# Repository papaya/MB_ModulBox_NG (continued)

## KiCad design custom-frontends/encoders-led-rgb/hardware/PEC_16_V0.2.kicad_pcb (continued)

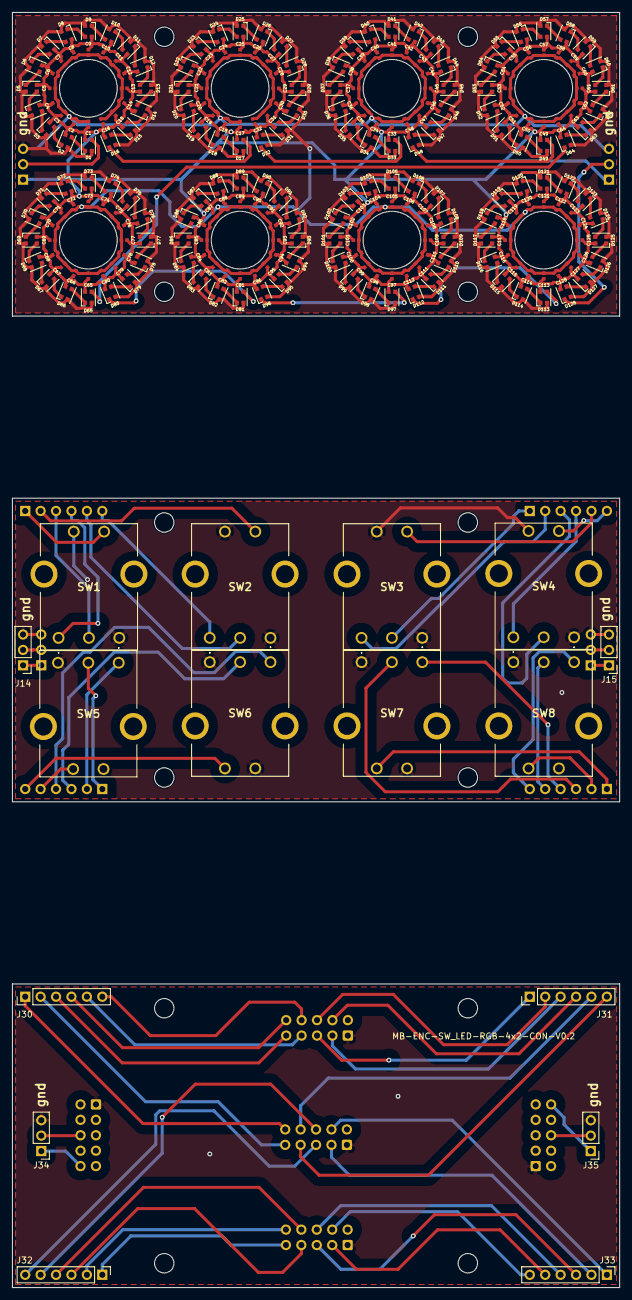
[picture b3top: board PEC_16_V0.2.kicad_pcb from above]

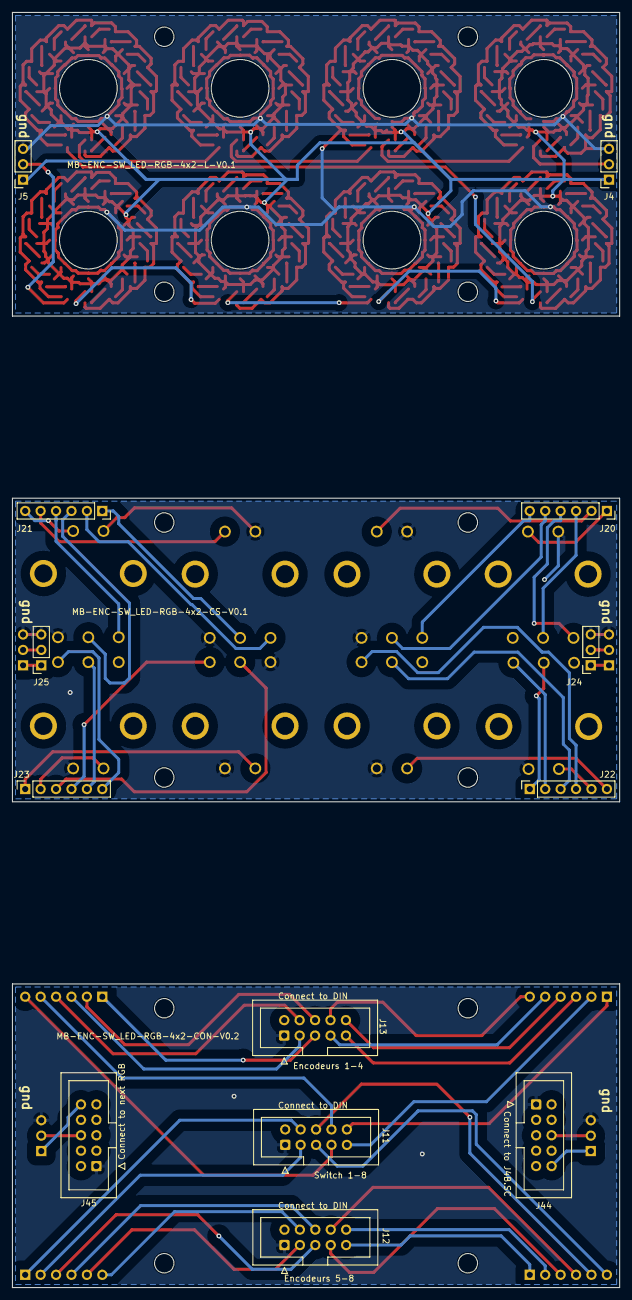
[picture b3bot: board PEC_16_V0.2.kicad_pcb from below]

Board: 2 copper layers, 100.0 x 50.0 mm, 305 parts (13 on the bottom side), 189 nets.

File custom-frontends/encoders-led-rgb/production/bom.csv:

Designator,Footprint,Quantity,Value,LCSC Part #
"C1, C10, C100, C101, C102, C103, C104, C105, C106, C107, C108, C109, C11, C110, C111, C112, C113, C114, C115, C116, C117, C118, C119, C12, C120, C121, C122, C123, C124, C125, C126, C127, C128, C13, C14, C15, C16, C17, C18, C19, C2, C20, C21, C22, C23, C24, C25, C26, C27, C28, C29, C3, C30, C31, C32, C33, C34, C35, C36, C37, C38, C39, C4, C40, C41, C42, C43, C44, C45, C46, C47, C48, C49, C5, C50, C51, C52, C53, C54, C55, C56, C57, C58, C59, C6, C60, C61, C62, C63, C64, C65, C66, C67, C68, C69, C7, C70, C71, C72, C73, C74, C75, C76, C77, C78, C79, C8, C80, C81, C82, C83, C84, C85, C86, C87, C88, C89, C9, C90, C91, C92, C93, C94, C95, C96, C97, C98, C99",CAPC1005X55N,128,100nf,C1525
"D1, D10, D100, D101, D102, D103, D104, D105, D106, D107, D108, D109, D11, D110, D111, D112, D113, D114, D115, D116, D117, D118, D119, D12, D120, D121, D122, D123, D124, D125, D126, D127, D128, D13, D14, D15, D16, D17, D18, D19, D2, D20, D21, D22, D23, D24, D25, D26, D27, D28, D29, D3, D30, D31, D32, D33, D34, D35, D36, D37, D38, D39, D4, D40, D41, D42, D43, D44, D45, D46, D47, D48, D49, D5, D50, D51, D52, D53, D54, D55, D56, D57, D58, D59, D6, D60, D61, D62, D63, D64, D65, D66, D67, D68, D69, D7, D70, D71, D72, D73, D74, D75, D76, D77, D78, D79, D8, D80, D81, D82, D83, D84, D85, D86, D87, D88, D89, D9, D90, D91, D92, D93, D94, D95, D96, D97, D98, D99",LED_WS2812B-2020_PLCC4_2.0x2.0mm,128,WS2812-2020,C2976072
"H1, H13, H14, H15, H16, H17, H18, H19, H2, H20, H3, H4",MountingHole_3.2mm_M3,12,MountingHole,
"H10, H11, H12, H5, H6, H7, H8, H9",Hole_9.5mm,8,MountingHole,
"J11, J12, J13",IDC-Header_2x05_P2.54mm_Vertical_ksr_dIN,3,sin_in,
"J14, J15, J34, J35",PinHeader_1x03_P2.54mm_Vertical,4,Conn_01x06_Pin,
"J20, J21, J22, J23",PinSocket_1x06_P2.54mm_Vertical,4,Conn_01x06_Socket,
"J24, J25, J4, J5",PinSocket_1x03_P2.54mm_Vertical,4,Conn_01x06_Socket,
"J30, J31, J32, J33",PinHeader_1x06_P2.54mm_Vertical,4,Conn_01x06_Pin,
"J44, J45",IDC-Header_2x05_P2.54mm_Vertical,2,IDC-Header_2x05_P2.54mm_Vertical,
"SW1, SW2, SW3, SW4, SW5, SW6, SW7, SW8",PEC164120FS0012,8,PEC16-4XXXF-SXXXX,

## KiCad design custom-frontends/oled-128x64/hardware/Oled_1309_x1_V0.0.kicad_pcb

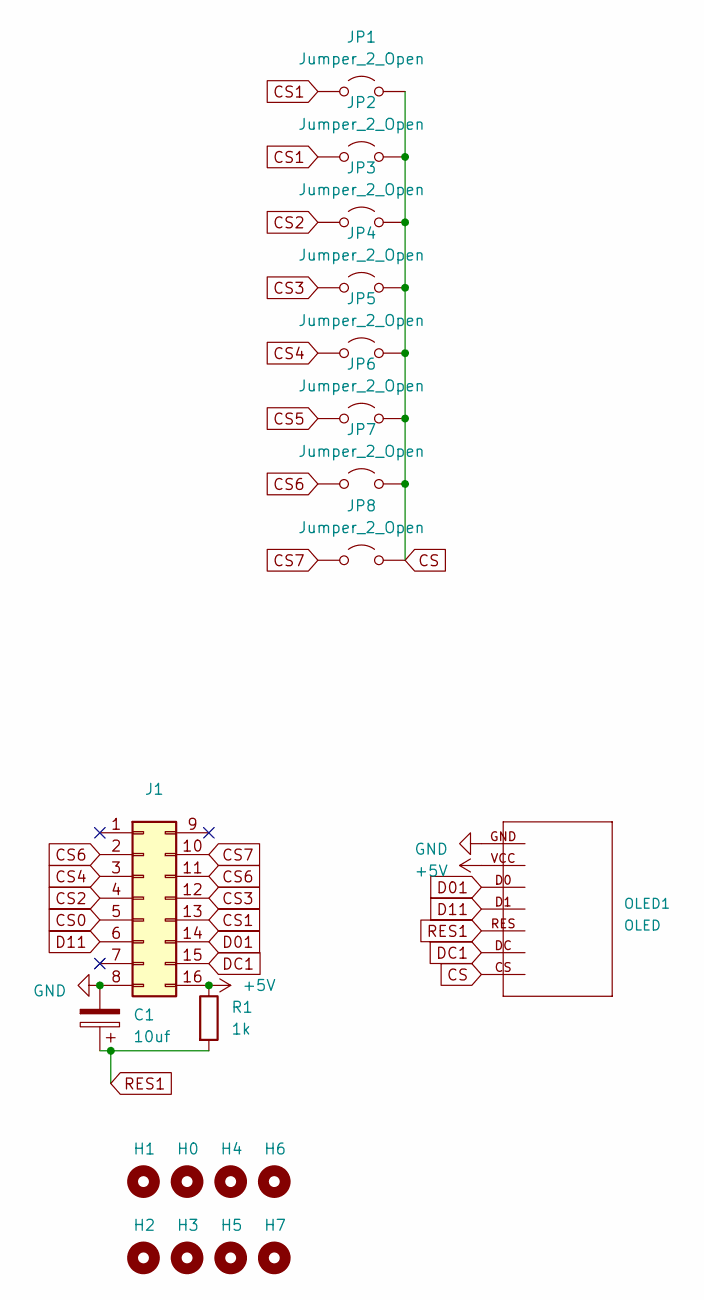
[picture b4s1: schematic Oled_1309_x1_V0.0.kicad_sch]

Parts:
C1: 10uf; CP_Radial_D5.0mm_P2.00mm
H0, H1, H2, H3, H4, H5, H6, H7: MountingHole; MountingHole_2.2mm_M2
J1: IDC-Header_2x08_P2.54mm_Vertical
JP1, JP2, JP3, JP4, JP5, JP6, JP7, JP8: Jumper_2_Open; PinHeader_1x02_P2.54mm_Vertical
OLED1: OLED; SSD_1309
R1: 1k; R_Axial_DIN0204_L3.6mm_D1.6mm_P5.08mm_Horizontal

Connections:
+5V: J1.16, OLED1.VCC, R1.1
CS: JP1.2 (B), JP2.2 (B), JP3.2 (B), JP4.2 (B), JP5.2 (B), JP6.2 (B), JP7.2 (B), JP8.2 (B), OLED1.CS
CS0: J1.5
CS1: J1.13, JP1.1 (A), JP2.1 (A)
CS2: J1.4, JP3.1 (A)
CS3: J1.12, JP4.1 (A)
CS4: J1.3, JP5.1 (A)
CS5: JP6.1 (A)
CS6: J1.2, J1.11, JP7.1 (A)
CS7: J1.10, JP8.1 (A)
D01: J1.14, OLED1.D0
D11: J1.6, OLED1.D1
DC1: J1.15, OLED1.DC
GND: C1.2, J1.8, OLED1.GND
RES1: C1.1, OLED1.RES, R1.2

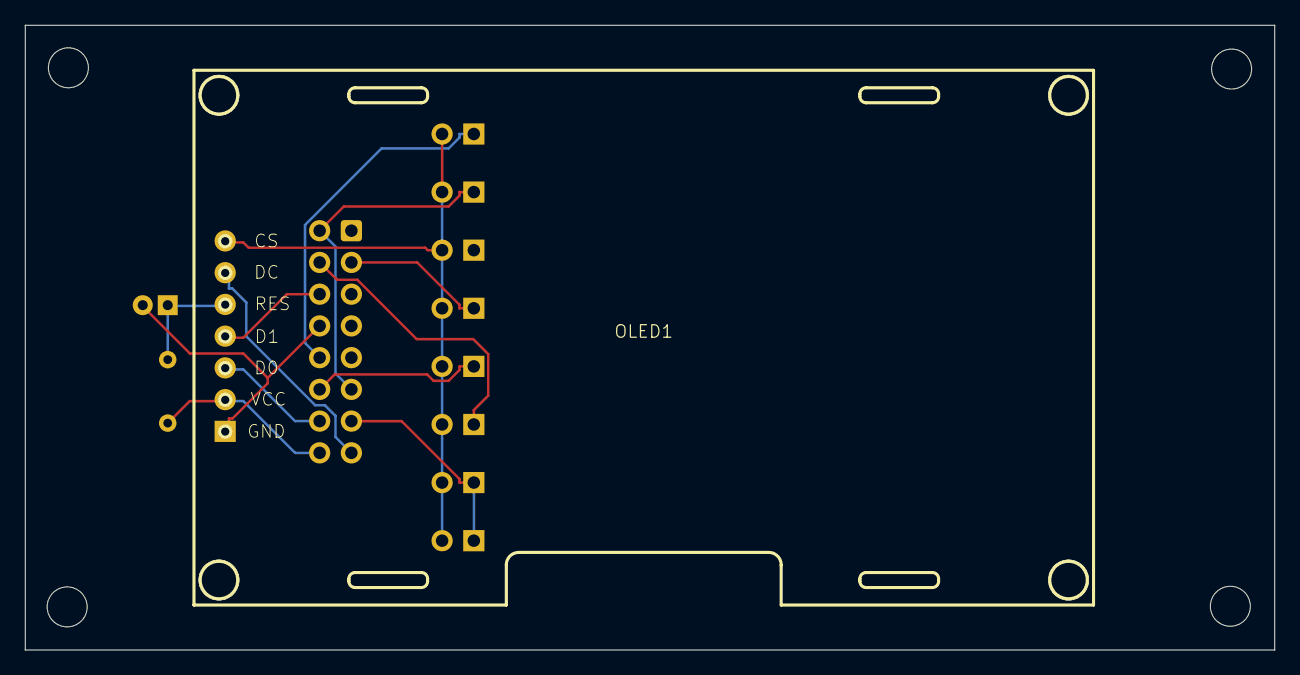
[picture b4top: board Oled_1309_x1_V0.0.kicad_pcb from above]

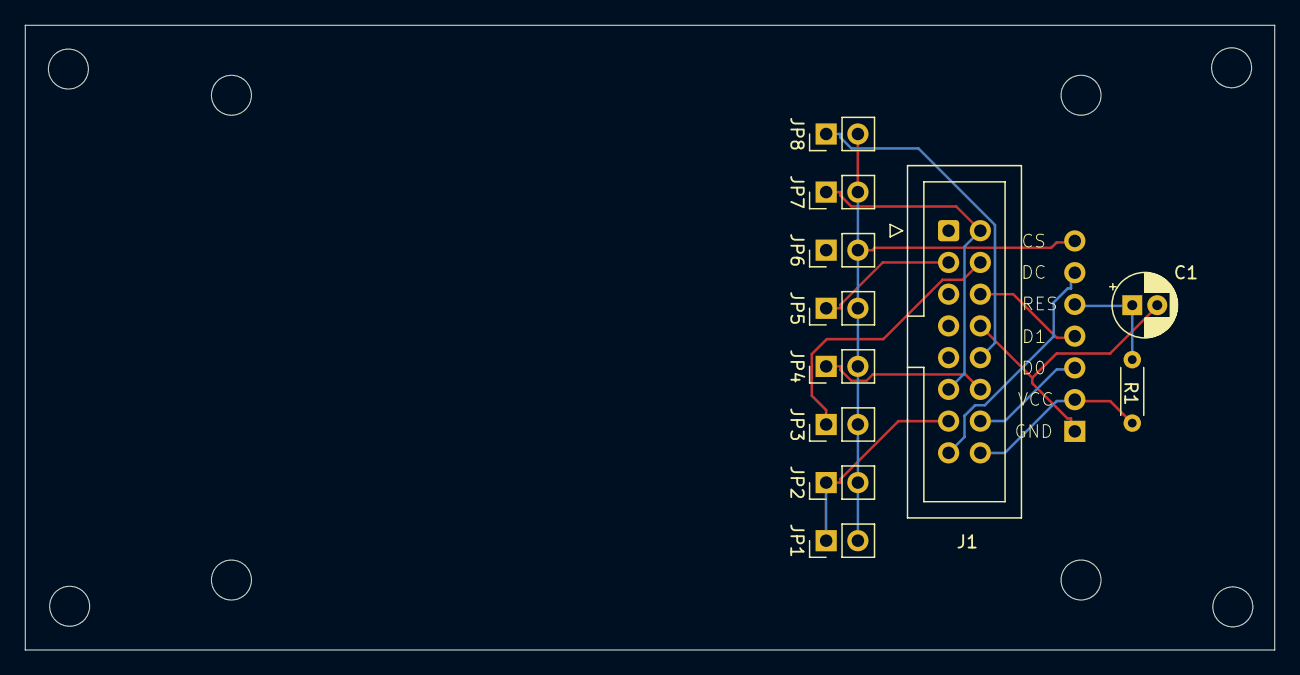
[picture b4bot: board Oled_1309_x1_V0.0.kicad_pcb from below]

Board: 2 copper layers, 100.0 x 50.0 mm, 20 parts (11 on the bottom side), 13 nets.

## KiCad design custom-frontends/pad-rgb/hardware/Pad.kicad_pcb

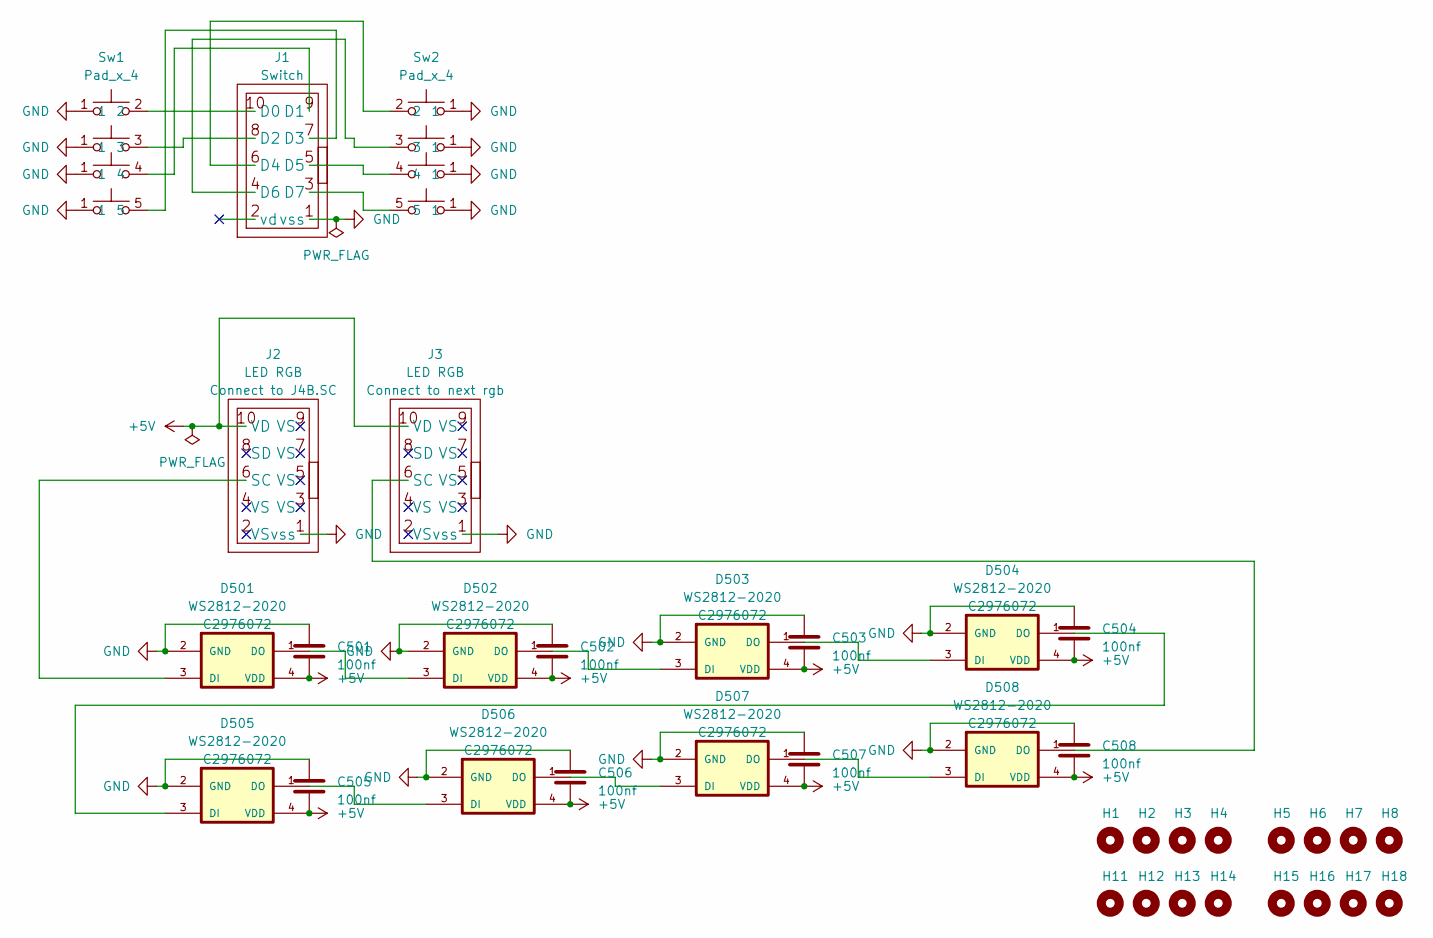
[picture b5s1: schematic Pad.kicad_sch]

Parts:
C501: 100nf; C_0402_1005Metric; JLCPCB Part # C1525
C502, C503, C504, C505, C506, C507, C508: 100nf; CAPC1005X55N; JLCPCB Part # C1525
D501, D502, D503, D504, D505, D506, D507, D508: WS2812-2020; LED_WS2812B-2020_PLCC4_2.0x2.0mm; JLCPCB Part # C2976072
H1, H2, H3, H4, H5, H6, H7, H8: MountingHole; MountingHole_2.2mm_M2
H11, H12, H13, H14, H15, H16, H17, H18: MountingHole; MountingHole_3mm
J1, J2, J3: IDC-Header_2x05_P2.54mm_Vertical
Sw1, Sw2: Pad_x_4; Pad x 4

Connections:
+5V: C501.2, C502.2, C503.2, C504.2, C505.2, C506.2, C507.2, C508.2, D501.4 (VDD), D502.4 (VDD), D503.4 (VDD), D504.4 (VDD), D505.4 (VDD), D506.4 (VDD), D507.4 (VDD), D508.4 (VDD), J2.10 (VD), J3.10 (VD)
GND: C501.1, C502.1, C503.1, C504.1, C505.1, C506.1, C507.1, C508.1, D501.2 (GND), D502.2 (GND), D503.2 (GND), D504.2 (GND), D505.2 (GND), D506.2 (GND), D507.2 (GND), D508.2 (GND), J1.1 (vss), J2.1 (vss), J3.1 (vss), Sw1.1, Sw2.1
unnamed: D501.3 (DI), J2.6 (SC)
unnamed: D501.1 (DO), D502.3 (DI)
unnamed: D502.1 (DO), D503.3 (DI)
unnamed: D503.1 (DO), D504.3 (DI)
unnamed: D504.1 (DO), D505.3 (DI)
unnamed: D505.1 (DO), D506.3 (DI)
unnamed: D506.1 (DO), D507.3 (DI)
unnamed: D507.1 (DO), D508.3 (DI)
unnamed: D508.1 (DO), J3.6 (SC)
unnamed: J1.10 (D0), Sw1.2
unnamed: J1.9 (D1), Sw1.4
unnamed: J1.8 (D2), Sw1.3
unnamed: J1.7 (D3), Sw1.5
unnamed: J1.6 (D4), Sw2.2
unnamed: J1.5 (D5), Sw2.4
unnamed: J1.4 (D6), Sw2.3
unnamed: J1.3 (D7), Sw2.5

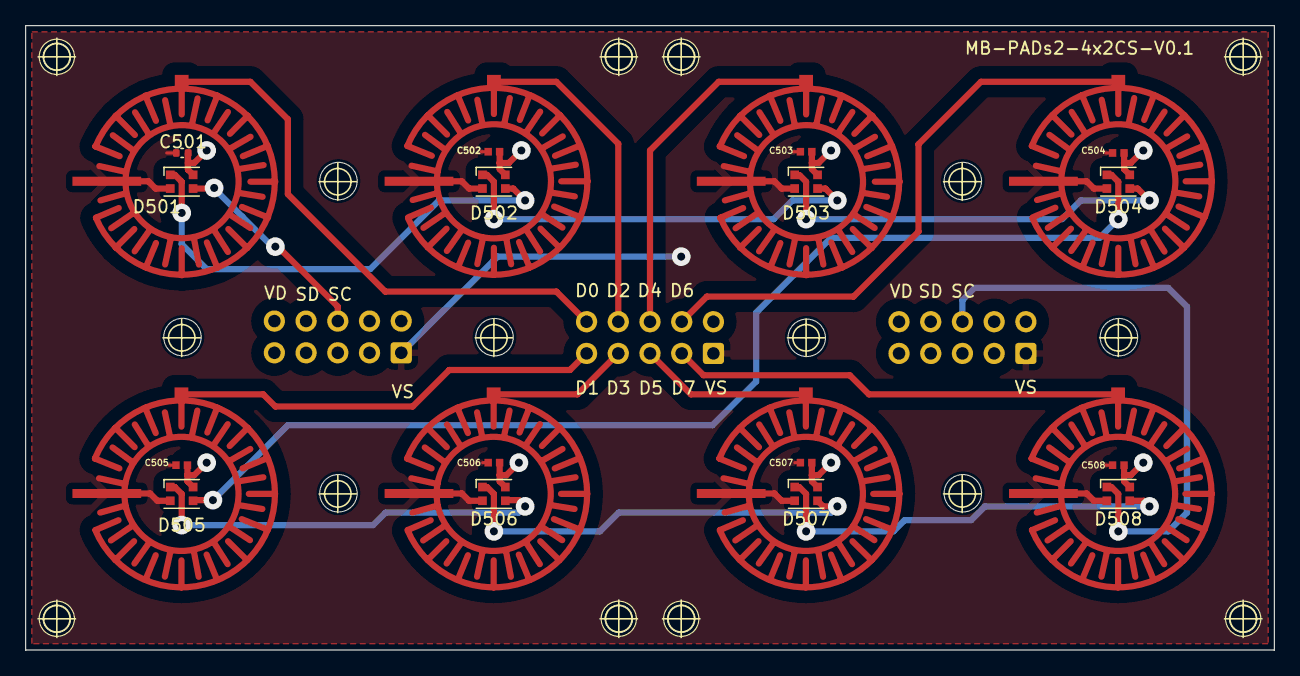
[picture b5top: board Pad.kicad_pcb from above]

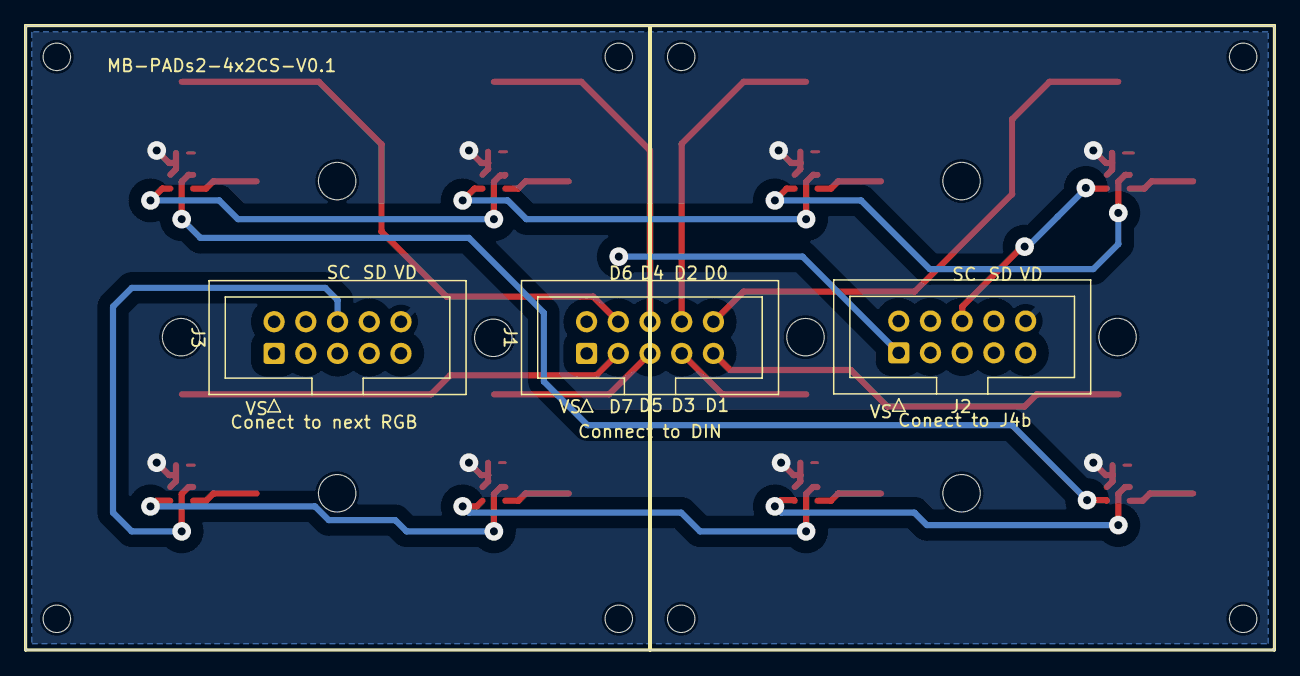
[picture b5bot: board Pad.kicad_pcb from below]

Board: 2 copper layers, 100.0 x 50.0 mm, 37 parts (3 on the bottom side), 19 nets.

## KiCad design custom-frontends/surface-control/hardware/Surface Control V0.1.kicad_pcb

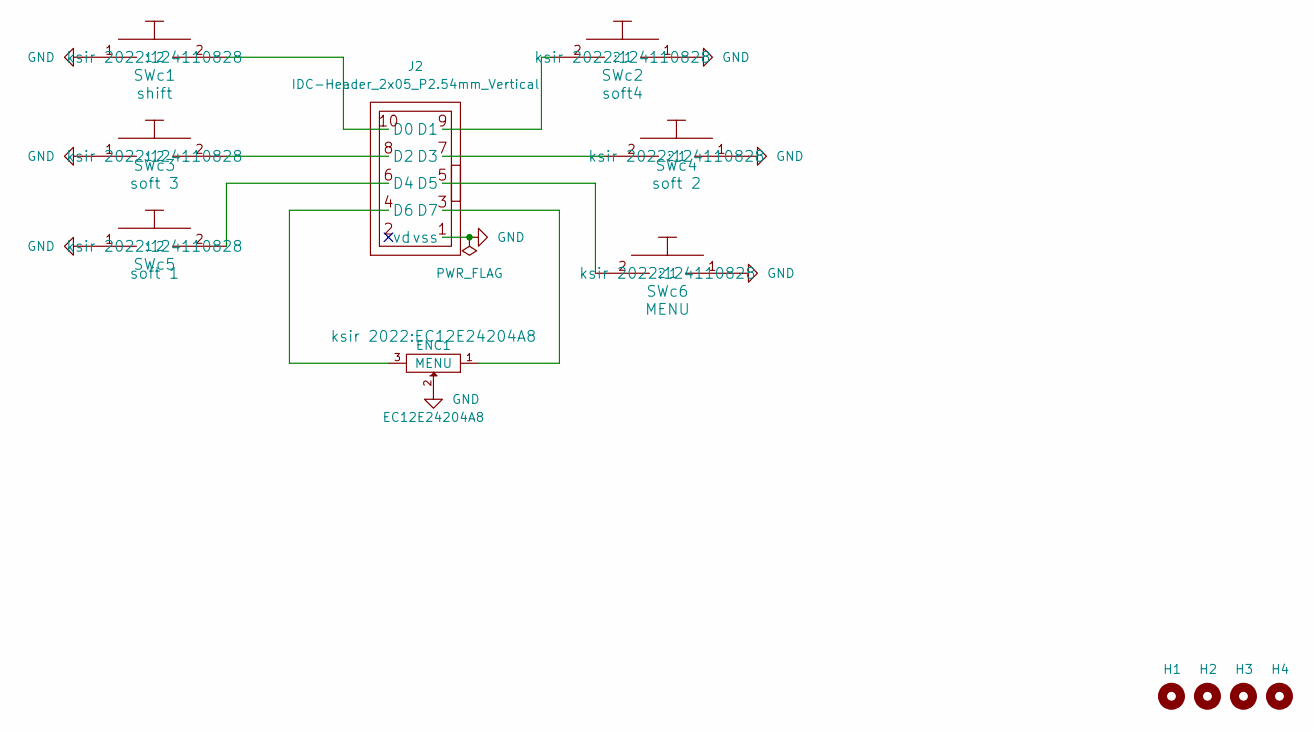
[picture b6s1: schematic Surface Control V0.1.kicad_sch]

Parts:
ENC1: MENU; EC12E24204A8
H1, H2, H3, H4: MountingHole; MountingHole_3.2mm_M3
J2: IDC-Header_2x05_P2.54mm_Vertical
SWc1: shift; 124110828
SWc2: soft4; 124110828
SWc3: soft 3; 124110828
SWc4: soft 2; 124110828
SWc5: soft 1; 124110828
SWc6: MENU; 124110828

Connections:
GND: ENC1.2, J2.1 (vss), SWc1.1, SWc2.1, SWc3.1, SWc4.1, SWc5.1, SWc6.1
unnamed: J2.10 (D0), SWc1.2
unnamed: J2.9 (D1), SWc2.2
unnamed: J2.8 (D2), SWc3.2
unnamed: J2.7 (D3), SWc4.2
unnamed: J2.6 (D4), SWc5.2
unnamed: J2.5 (D5), SWc6.2
unnamed: ENC1.3, J2.4 (D6)
unnamed: ENC1.1, J2.3 (D7)

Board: 2 copper layers, 16 parts (1 on the bottom side), 9 nets, no tracks yet.

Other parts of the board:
H3#2, H3#3, H3#4, H3#5: MountingHole; MountingHole_3.2mm_M3
